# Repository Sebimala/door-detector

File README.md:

# ESP32-S3 Door Sensor

A low-power smart door sensor using a Seeed Studio XIAO ESP32-S3, reed switch, and CR2032 battery[cite: 1, 2].

## 🛠️ Components
* **MCU:** Seeed Studio XIAO ESP32-S3[cite: 1, 2]
* **Sensor:** Reed Switch (`SW1`) on pin `D0`[cite: 1, 2]
* **Power:** CR2032 Battery (`BT1`)[cite: 1, 2]
* **Capacitors:** `C1` (filtering) and `C2` (decoupling)[cite: 1, 2]
* **Test Points:** `TP1` (Signal), `TP2` (`BAT_VIN`), `TP3` (`GND`)[cite: 1, 2]

## 🚀 Quick Setup
1. Open `Door.kicad_sch` in KiCad[cite: 3].
2. Run **ERC** to verify 0 errors[cite: 5].
3. Press **`F8`** to update the PCB layout[cite: 8].

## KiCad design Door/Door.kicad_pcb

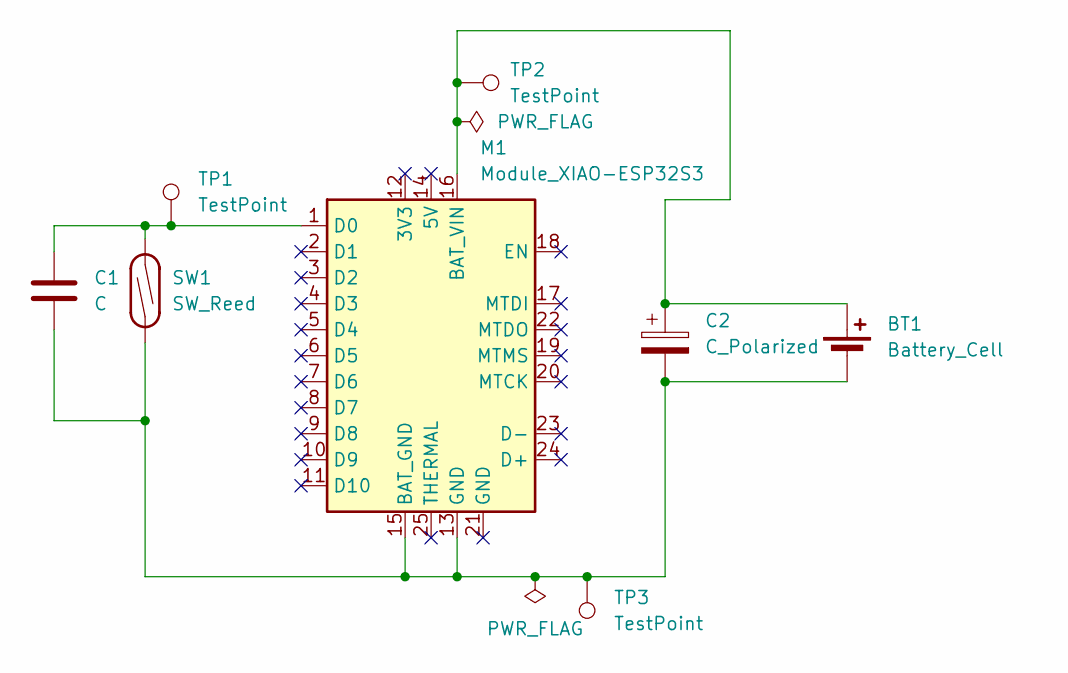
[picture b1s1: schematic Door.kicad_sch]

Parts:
BT1: Battery_Cell; BatteryHolder_Keystone_1057_1x2032
C1: C; C_0805_2012Metric_Pad1.18x1.45mm_HandSolder
C2: C_Polarized; C_Elec_6.3x5.4
M1: Module_XIAO-ESP32S3; SeeedStudio_XIAO_ESP32S3
SW1: SW_Reed; PinHeader_1x02_P2.54mm_Vertical
TP1, TP2, TP3: TestPoint; TestPoint_Pad_D2.0mm

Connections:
unnamed: BT1.1 (+), C2.1, M1.16 (BAT_VIN), TP2.1 (1_1)
unnamed: BT1.2 (-), C1.1, C2.2, M1.13 (GND), M1.15 (BAT_GND), SW1.1, TP3.1 (1_1)
unnamed: C1.2, M1.1 (D0), SW1.2, TP1.1 (1_1)

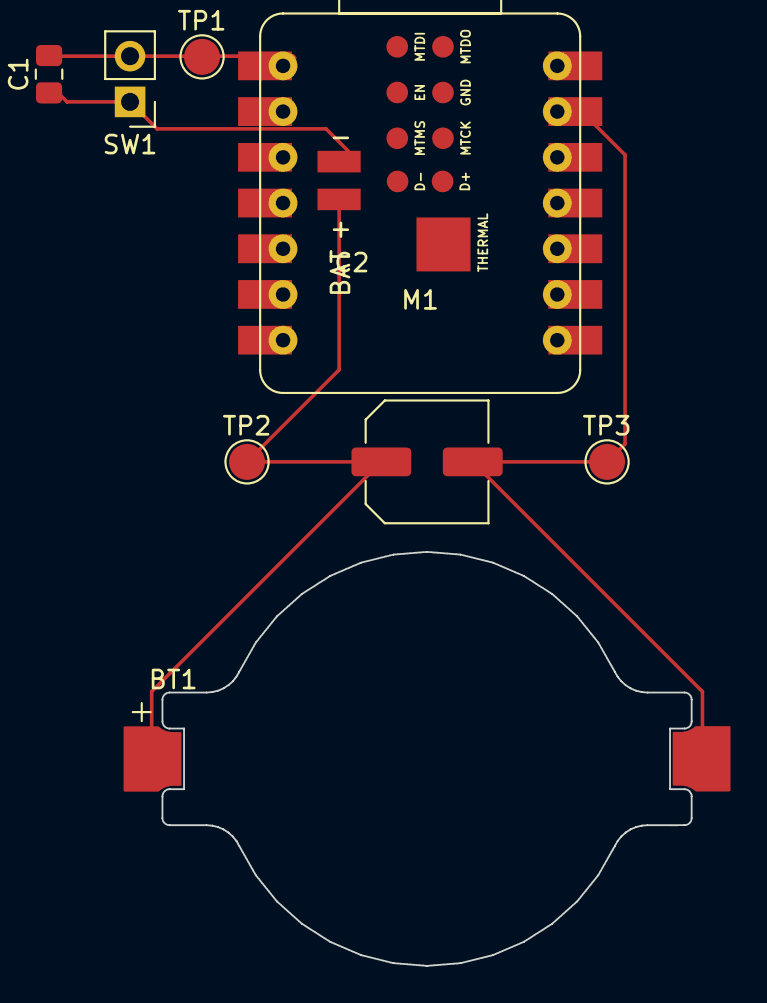
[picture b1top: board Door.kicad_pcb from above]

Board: 2 copper layers, 29.4 x 23.0 mm, 8 parts (0 on the bottom side), 3 nets.
